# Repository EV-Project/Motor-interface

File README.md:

# Motor-interface

## Description
This motor-interface board is used to connect motor and motor controller.

## Requirements
Power: 96V Current: 400A
Connections: PC USB 
Safety: Fuse
Survivability: IP 6/7
Size: square or retangular

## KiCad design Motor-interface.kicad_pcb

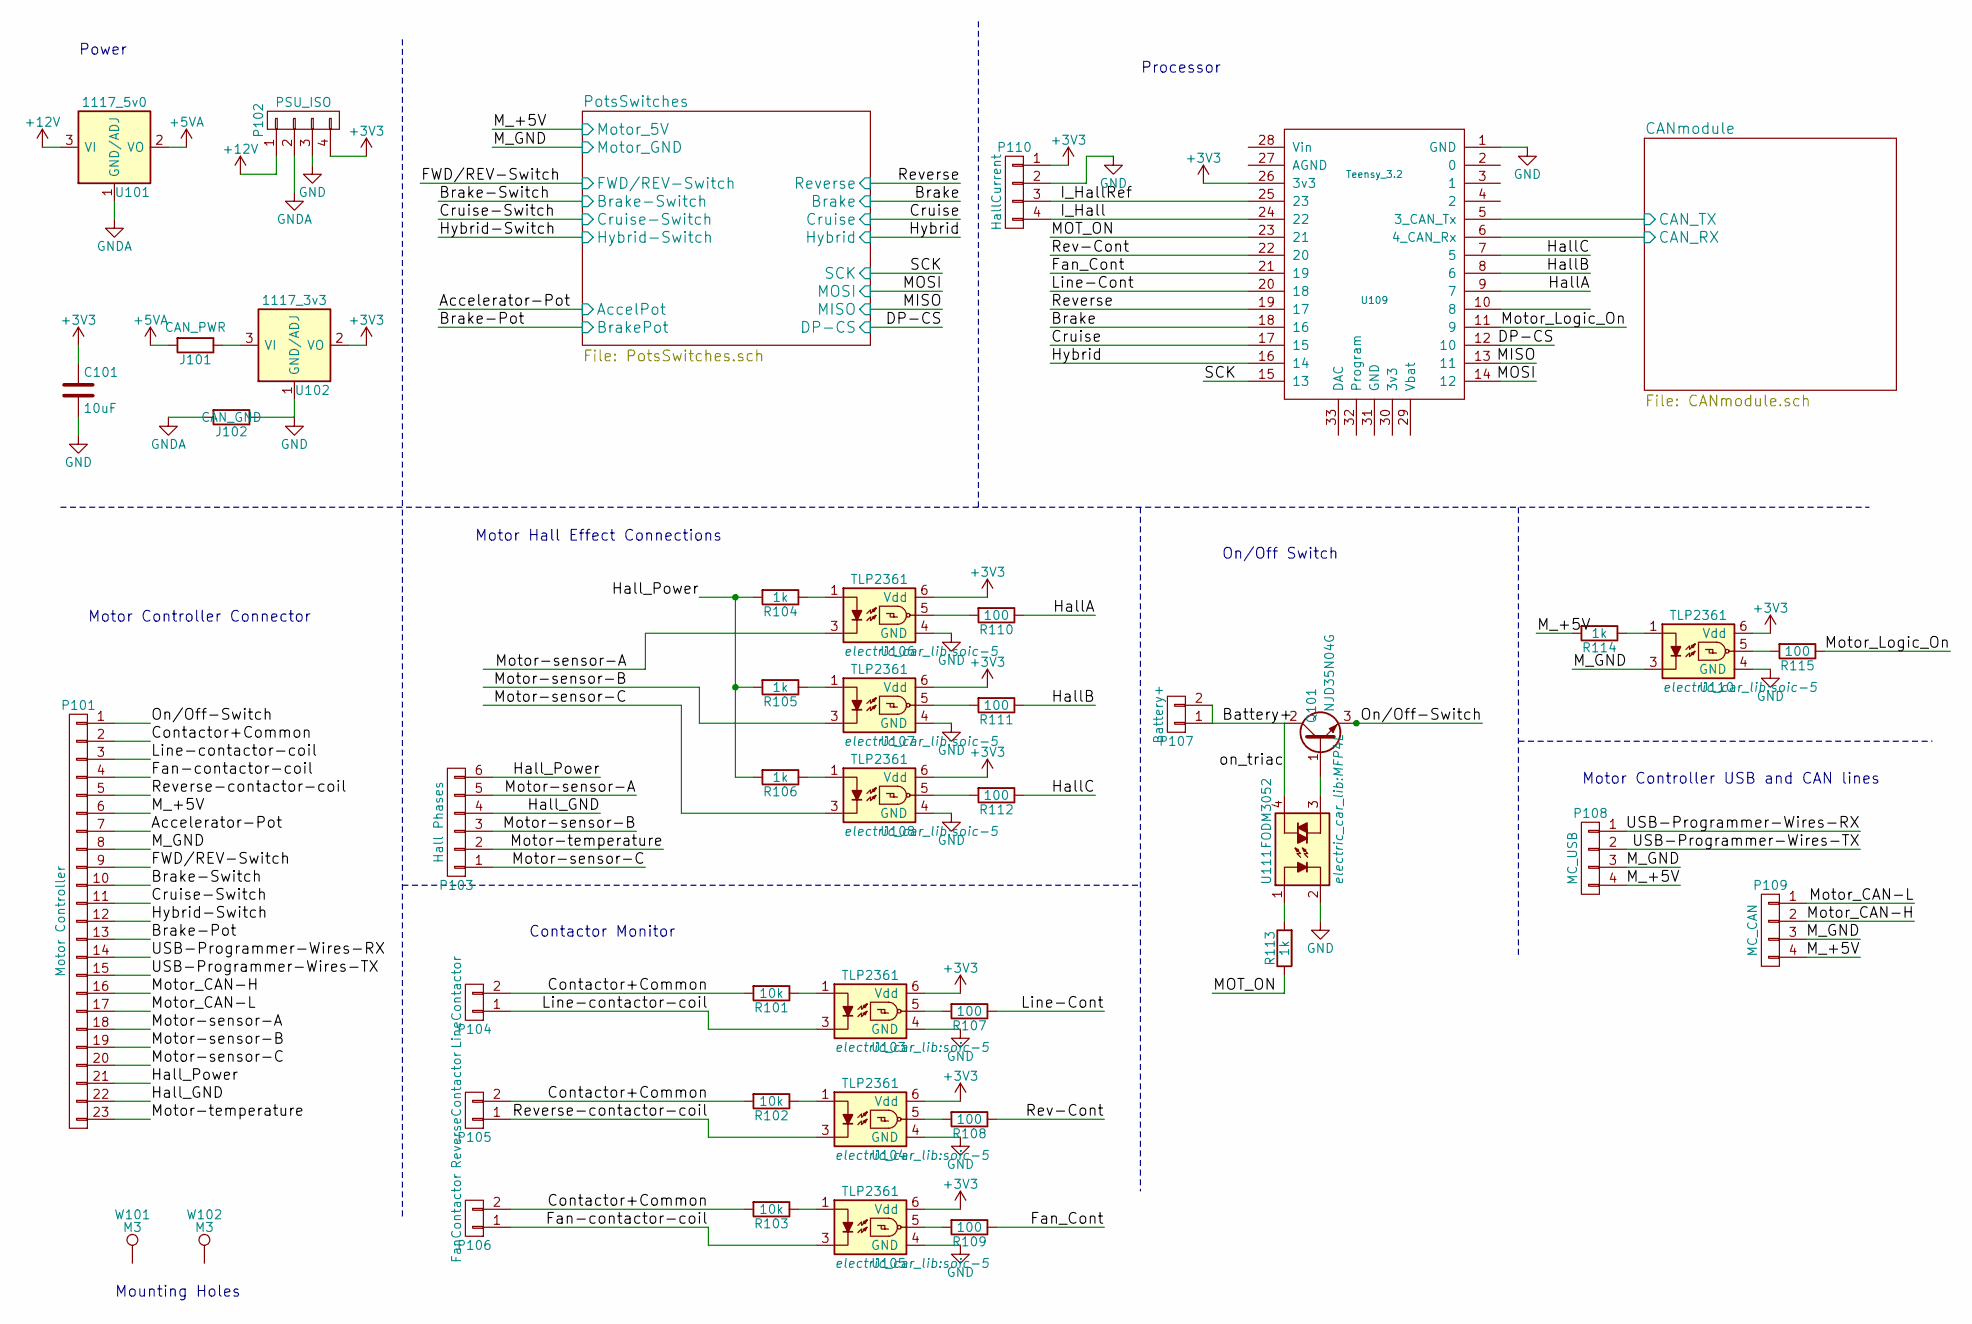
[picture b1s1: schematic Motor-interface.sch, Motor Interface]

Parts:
C101: 10uF; C_1210_HandSoldering
J101: CAN_PWR; R_1210_HandSoldering
J102: CAN_GND; R_1210_HandSoldering
P101: Motor Controller; TE_23_pins_776087-1_connector
P102: PSU_ISO; Pin_Header_Straight_1x04
P103: Hall Phases; Pin_Header_Angled_2x03
P104: LineContactor; bornier2
P105: ReverseContactor; bornier2
P106: FanContactor; bornier2
P107: Battery+; bornier2
P108: MC_USB; Pin_Header_Straight_1x04
P109: MC_CAN; Pin_Header_Straight_1x04
P110: HallCurrent; Pin_Header_Straight_1x04
Q101: NJD35N04G; SOT-428
R101, R102, R103: 10k; R_1206_HandSoldering
R104, R105, R106, R113, R114: 1k; R_1206_HandSoldering
R107, R108, R109, R110, R111, R112, R115: 100; R_1206_HandSoldering
U101: 1117_5v0; SOT-223
U102: 1117_3v3; SOT-223
U103, U104, U105, U106, U107, U108, U110: TLP2361; soic-5
U109: Teensy_3.2; Teensy3.2
U111: FODM3052; MFP4L
W101, W102: M3; MountingHole_3.5mm_Pad_Via

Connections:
+3V3: C101.1, P102.4, P110.1, U102.2 (VO), U103.6 (Vdd), U104.6 (Vdd), U105.6 (Vdd), U106.6 (Vdd), U107.6 (Vdd), U108.6 (Vdd), U109.26 (3v3), U110.6 (Vdd); also elsewhere on the board
+5VA: J101.2, U101.2 (VO); also elsewhere on the board
+12V: P102.1, U101.3 (VI); also elsewhere on the board
/Accelerator-Pot: P101.7; also elsewhere on the board
/Battery+: P107.1, P107.2, Q101.2 (C), U111.4
/Brake: U109.18 (16); also elsewhere on the board
/Brake-Pot: P101.13; also elsewhere on the board
/Brake-Switch: P101.10; also elsewhere on the board
/CANmodule/CAN_RX: U109.6 (4_CAN_Rx); also elsewhere on the board
/CANmodule/CAN_TX: U109.5 (3_CAN_Tx); also elsewhere on the board
/Contactor+Common: P101.2, P104.2, P105.2, P106.2, R101.2, R102.2, R103.2
/Cruise: U109.17 (15); also elsewhere on the board
/Cruise-Switch: P101.11; also elsewhere on the board
/DP-CS: U109.12 (10); also elsewhere on the board
/FWD/REV-Switch: P101.9; also elsewhere on the board
/Fan-contactor-coil: P101.4, P106.1, U105.3
/Fan_Cont: R109.1, U109.21 (19)
/HallA: R110.1, U109.9 (7)
/HallB: R111.1, U109.8 (6)
/HallC: R112.1, U109.7 (5)
/Hall_GND: P101.22, P103.4
/Hall_Power: P101.21, P103.6, R104.2, R105.2, R106.2
/Hybrid: U109.16 (14); also elsewhere on the board
/Hybrid-Switch: P101.12; also elsewhere on the board
/I_Hall: P110.4, U109.24 (22)
/I_HallRef: P110.3, U109.25 (23)
/Line-Cont: R107.1, U109.20 (18)
/Line-contactor-coil: P101.3, P104.1, U103.3
/MISO: U109.13 (11); also elsewhere on the board
/MOSI: U109.14 (12); also elsewhere on the board
/MOT_ON: R113.1, U109.23 (21)
/M_+5V: P101.6, P108.4, P109.4, R114.2; also elsewhere on the board
/M_GND: P101.8, P108.3, P109.3, U110.3; also elsewhere on the board
/Motor-sensor-A: P101.18, P103.5, U106.3
/Motor-sensor-B: P101.19, P103.3, U107.3
/Motor-sensor-C: P101.20, P103.1, U108.3
/Motor-temperature: P101.23, P103.2
/Motor_CAN-H: P101.16, P109.2
/Motor_CAN-L: P101.17, P109.1
/Motor_Logic_On: R115.1, U109.11 (9)
/On/Off-Switch: P101.1, Q101.3 (E)
/Rev-Cont: R108.1, U109.22 (20)
/Reverse: U109.19 (17); also elsewhere on the board
/Reverse-contactor-coil: P101.5, P105.1, U104.3
/SCK: U109.15 (13); also elsewhere on the board
/USB-Programmer-Wires-RX: P101.14, P108.1
/USB-Programmer-Wires-TX: P101.15, P108.2
GND: C101.2, J102.1, P102.3, P110.2, U102.1 (GND/ADJ), U103.4 (GND), U104.4 (GND), U105.4 (GND), U106.4 (GND), U107.4 (GND), U108.4 (GND), U109.1 (GND), U110.4 (GND), U111.2; also elsewhere on the board
GNDA: J102.2, P102.2, U101.1 (GND/ADJ); also elsewhere on the board
unnamed: J101.1, U102.3 (VI)
unnamed: Q101.1 (B), U111.3
unnamed: R101.1, U103.1
unnamed: R102.1, U104.1
unnamed: R103.1, U105.1
unnamed: R104.1, U106.1
unnamed: R105.1, U107.1
unnamed: R106.1, U108.1
unnamed: R107.2, U103.5
unnamed: R108.2, U104.5
unnamed: R109.2, U105.5
unnamed: R110.2, U106.5
unnamed: R111.2, U107.5
unnamed: R112.2, U108.5
unnamed: R113.2, U111.1
unnamed: R114.1, U110.1
unnamed: R115.2, U110.5

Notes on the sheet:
On/Off Switch
Contactor Monitor
Processor
Motor Hall Effect Connections
Motor Controller USB and CAN lines
Power
Motor Controller Connector
Mounting Holes

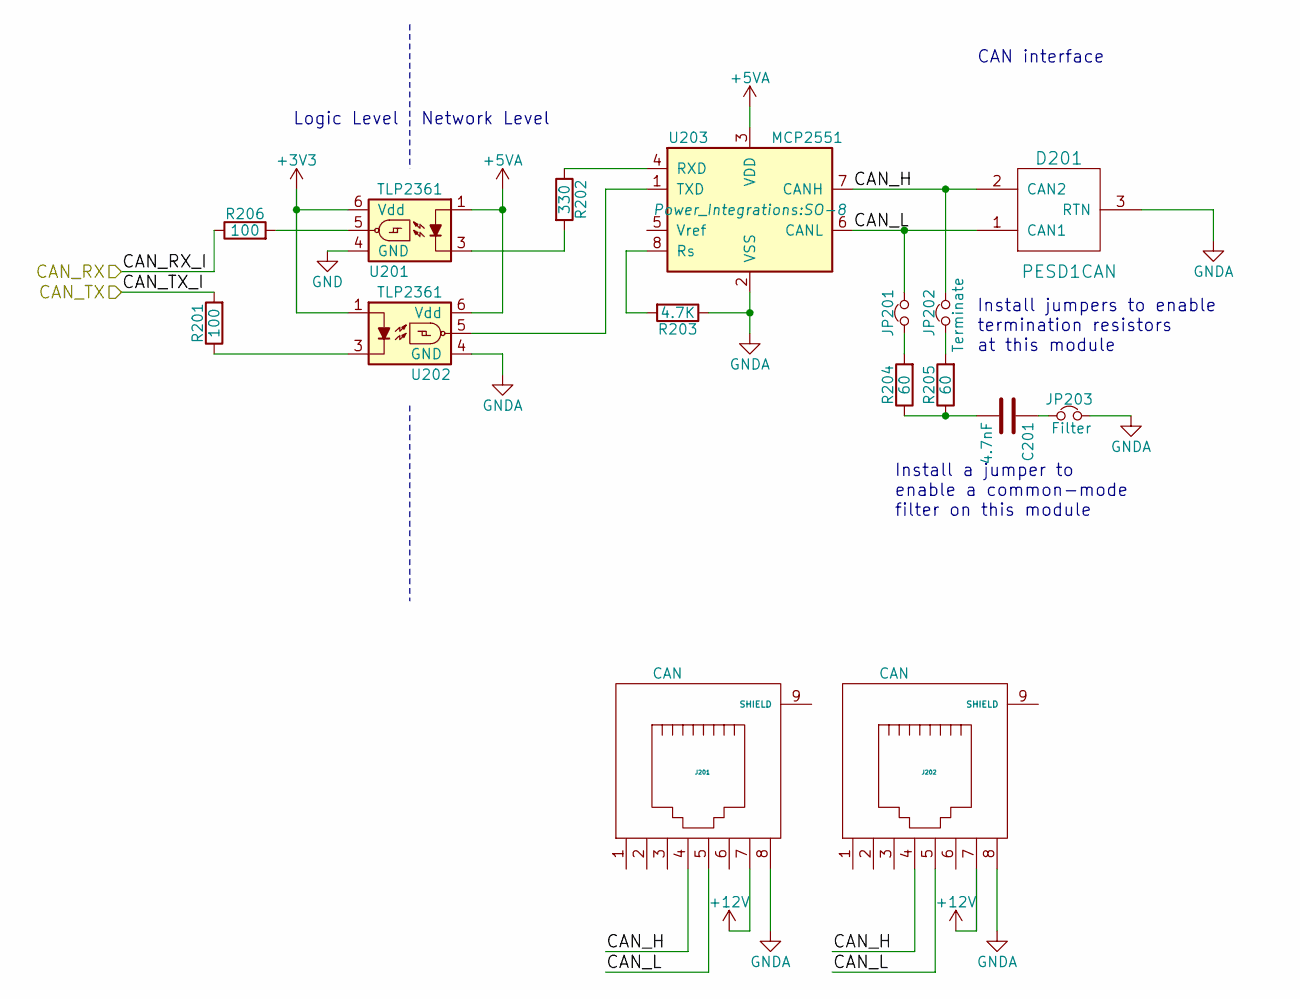
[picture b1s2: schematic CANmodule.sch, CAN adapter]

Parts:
C201: 4.7nF; C_1210_HandSoldering
D201: PESD1CAN; SOT-23_Handsoldering
J201, J202: CAN; RJ45_8
JP201, JP202: Terminate; JumperSingle
JP203: Filter; JumperSingle
R201, R206: 100; R_1206_HandSoldering
R202: 330; R_1206_HandSoldering
R203: 4.7K; R_1206_HandSoldering
R204, R205: 60; R_1210_HandSoldering
U201, U202: TLP2361; soic-5
U203: MCP2551; SO-8

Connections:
+3V3: U201.6 (Vdd), U202.1; also elsewhere on the board
+5VA: U201.1, U202.6 (Vdd), U203.3 (VDD); also elsewhere on the board
+12V: J201.7, J202.7; also elsewhere on the board
/CANmodule/CAN_H: D201.2 (CAN2), J201.4, J202.4, JP202.1, U203.7 (CANH)
/CANmodule/CAN_L: D201.1 (CAN1), J201.5, J202.5, JP201.2, U203.6 (CANL)
/CANmodule/CAN_RX: R206.1; also elsewhere on the board
/CANmodule/CAN_TX: R201.2; also elsewhere on the board
GND: U201.4 (GND); also elsewhere on the board
GNDA: D201.3 (RTN), J201.8, J202.8, JP203.2, R203.1, U202.4 (GND), U203.2 (VSS); also elsewhere on the board
unnamed: C201.1, JP203.1
unnamed: C201.2, R204.1, R205.1
unnamed: JP201.1, R204.2
unnamed: JP202.2, R205.2
unnamed: R201.1, U202.3
unnamed: R202.1, U203.4 (RXD)
unnamed: R202.2, U201.3
unnamed: R203.2, U203.8 (Rs)
unnamed: R206.2, U201.5
unnamed: U202.5, U203.1 (TXD)

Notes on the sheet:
Logic Level
Network Level
Install jumpers to enable termination resistors at this module
Install a jumper to enable a common-mode filter on this module
CAN interface

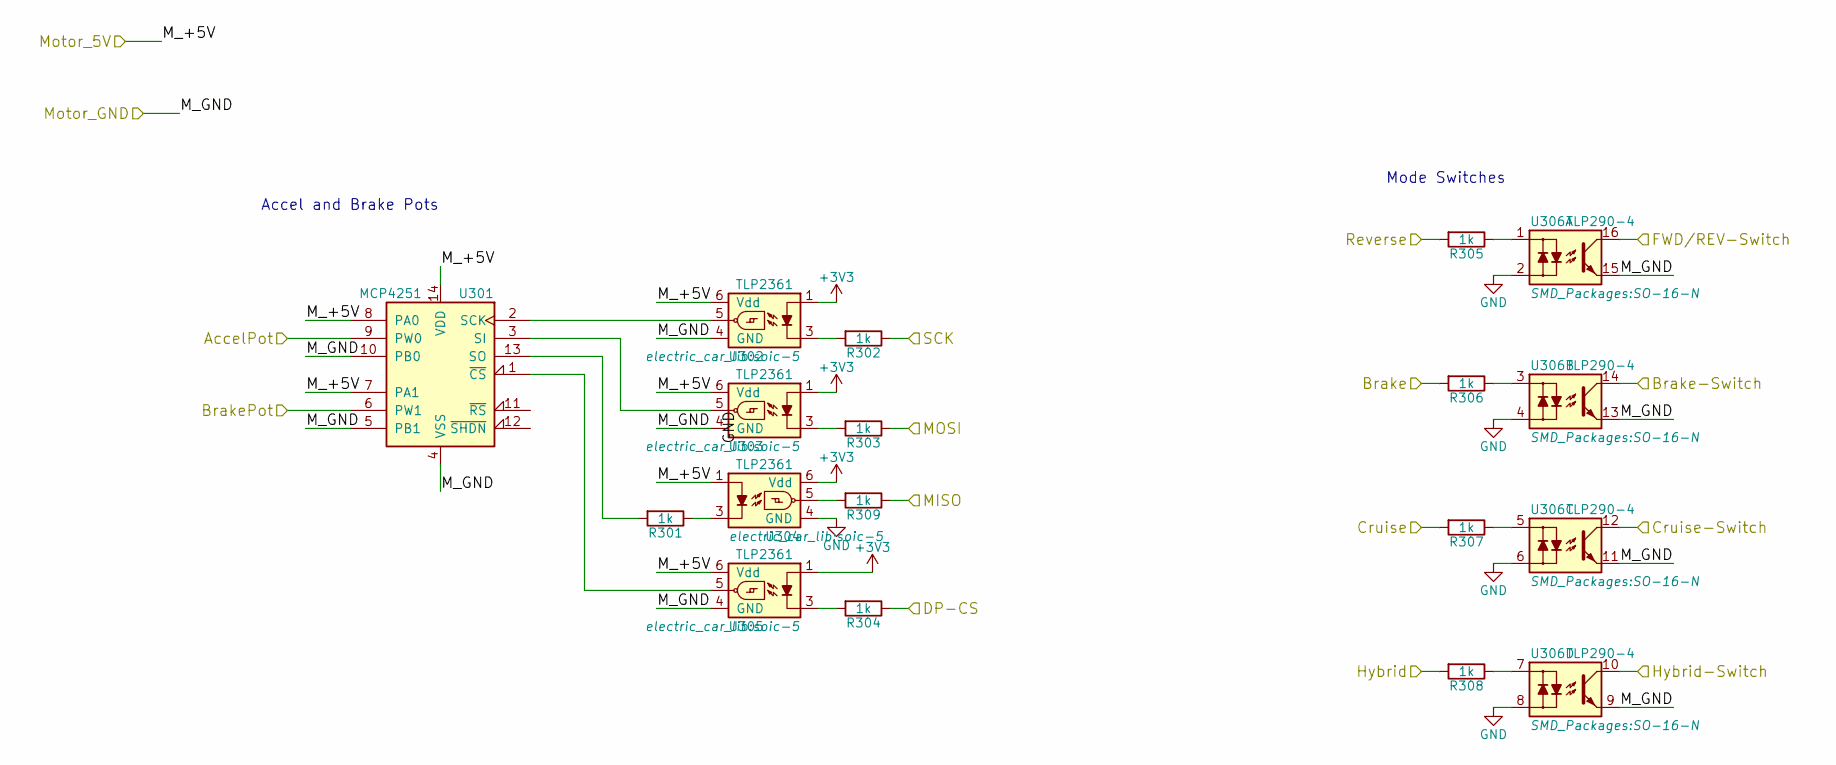
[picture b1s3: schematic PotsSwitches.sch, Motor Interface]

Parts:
R301, R302, R303, R304, R305, R306, R307, R308, R309: 1k; R_1206_HandSoldering
U301: MCP4251; SOIC-14_N
U302, U303, U304, U305: TLP2361; soic-5
U306: TLP290-4; SO-16-N

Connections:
+3V3: U302.1, U303.1, U304.6 (Vdd), U305.1; also elsewhere on the board
/Accelerator-Pot: U301.9 (PW0); also elsewhere on the board
/Brake: R306.2; also elsewhere on the board
/Brake-Pot: U301.6 (PW1); also elsewhere on the board
/Brake-Switch: U306.14; also elsewhere on the board
/Cruise: R307.2; also elsewhere on the board
/Cruise-Switch: U306.12; also elsewhere on the board
/DP-CS: R304.1; also elsewhere on the board
/FWD/REV-Switch: U306.16; also elsewhere on the board
/Hybrid: R308.2; also elsewhere on the board
/Hybrid-Switch: U306.10; also elsewhere on the board
/MISO: R309.1; also elsewhere on the board
/MOSI: R303.1; also elsewhere on the board
/M_+5V: U301.7 (PA1), U301.8 (PA0), U301.14 (VDD), U302.6 (Vdd), U303.6 (Vdd), U304.1, U305.6 (Vdd); also elsewhere on the board
/M_GND: U301.4 (VSS), U301.5 (PB1), U301.10 (PB0), U302.4 (GND), U303.4 (GND), U305.4 (GND), U306.9, U306.11, U306.13, U306.15; also elsewhere on the board
/Reverse: R305.2; also elsewhere on the board
/SCK: R302.1; also elsewhere on the board
GND: U304.4 (GND), U306.2, U306.4, U306.6, U306.8; also elsewhere on the board
unnamed: R301.1, U304.3
unnamed: R301.2, U301.13 (SO)
unnamed: R302.2, U302.3
unnamed: R303.2, U303.3
unnamed: R304.2, U305.3
unnamed: R305.1, U306.1
unnamed: R306.1, U306.3
unnamed: R307.1, U306.5
unnamed: R308.1, U306.7
unnamed: R309.2, U304.5
unnamed: U301.1 (~CS), U305.5
unnamed: U301.2 (SCK), U302.5
unnamed: U301.3 (SI), U303.5

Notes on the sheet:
Accel and Brake Pots
Mode Switches

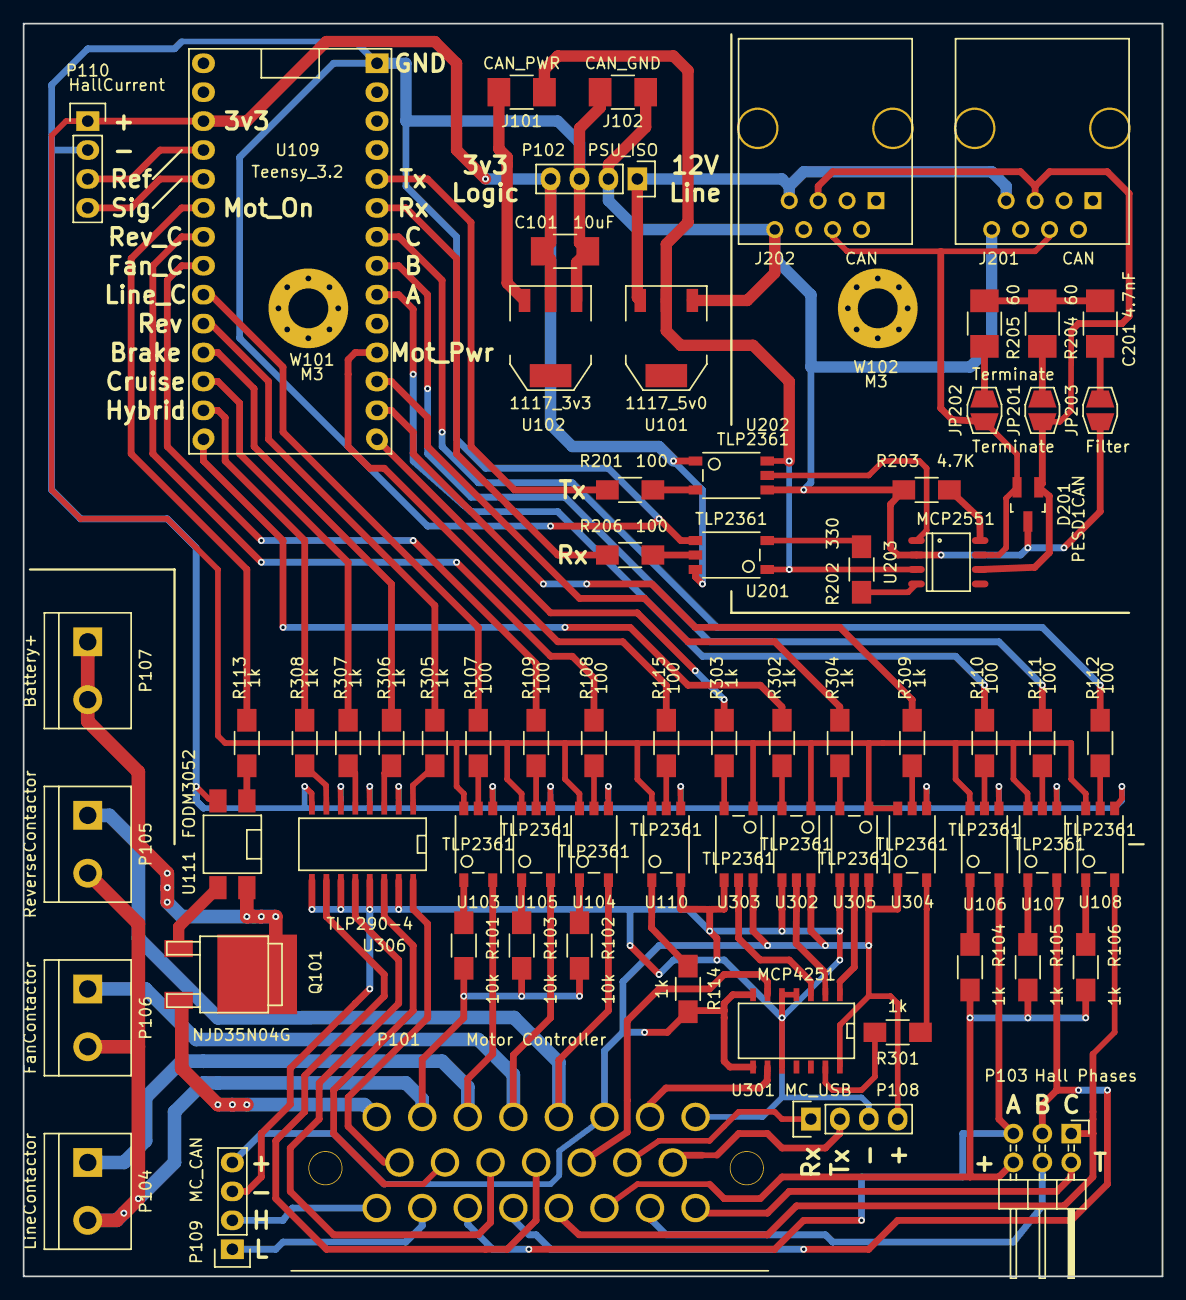
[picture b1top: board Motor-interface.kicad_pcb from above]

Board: 2 copper layers, 100.0 x 110.0 mm, 73 parts (0 on the bottom side), 91 nets.

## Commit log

2016-10-11 created a generic CAN module
2016-10-11 added digital pot
2016-10-18 edited wiring
2016-10-25 Ev-Overview
2016-10-25 Added TE 23pins and netlist
2016-11-01 mode switches and coil contactors
2016-11-08 added hall effect connector and USB and CAN lines
2016-11-15 added hall-uC resistors for speed monitoring
2016-11-15 Isolated the Motor Controller, added PSU
2016-11-15 most associations, started pcb
2016-11-15 removed files from other repo
2016-11-15 PBC layout
2016-11-16 changed optos, removed relay, needs ssr
2016-11-16 minor tweaks, started layout
2016-11-16 swapped pins, arranged parts
2016-11-16 laid out CAN hardware
2016-11-16 laid out halls and pots
2016-11-16 laid out Contactors and monitors
2016-11-16 fixed triac, passed DRC
2016-11-16 renamed transistor
2016-11-16 renamed transistor (fixed)
2016-11-17 silkscreen changes
2016-11-17 pour and silk edits
2016-11-17 plotted gerbers
2016-11-17 adjusted gerbers, exported pngs from gerblook.org
2016-11-17 renamed production files
2016-11-17 adjusted via sized
2016-11-17 changed file extensions
2016-11-30 added schematic PDFs
